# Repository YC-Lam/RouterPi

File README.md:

# RouterPi

A modular router development board based on the raspberry pi compute module 5.

Features:
- 2x 2.5G Ethernet Wan/Lan port
- 2x Gigabyte Ethernet Lan port
- M.2 E key connector for AP module
- RTC battery
- PWM fan connector
- SD card slot for compute module lite
- 12-24v input voltage

# Design constraints
- minimal track width: 0.127 mm
- minimal clearance: 0.125 mm
- minimal via hole diameter: 0.3 mm
- minimal via ring diameter: 0.45 mm

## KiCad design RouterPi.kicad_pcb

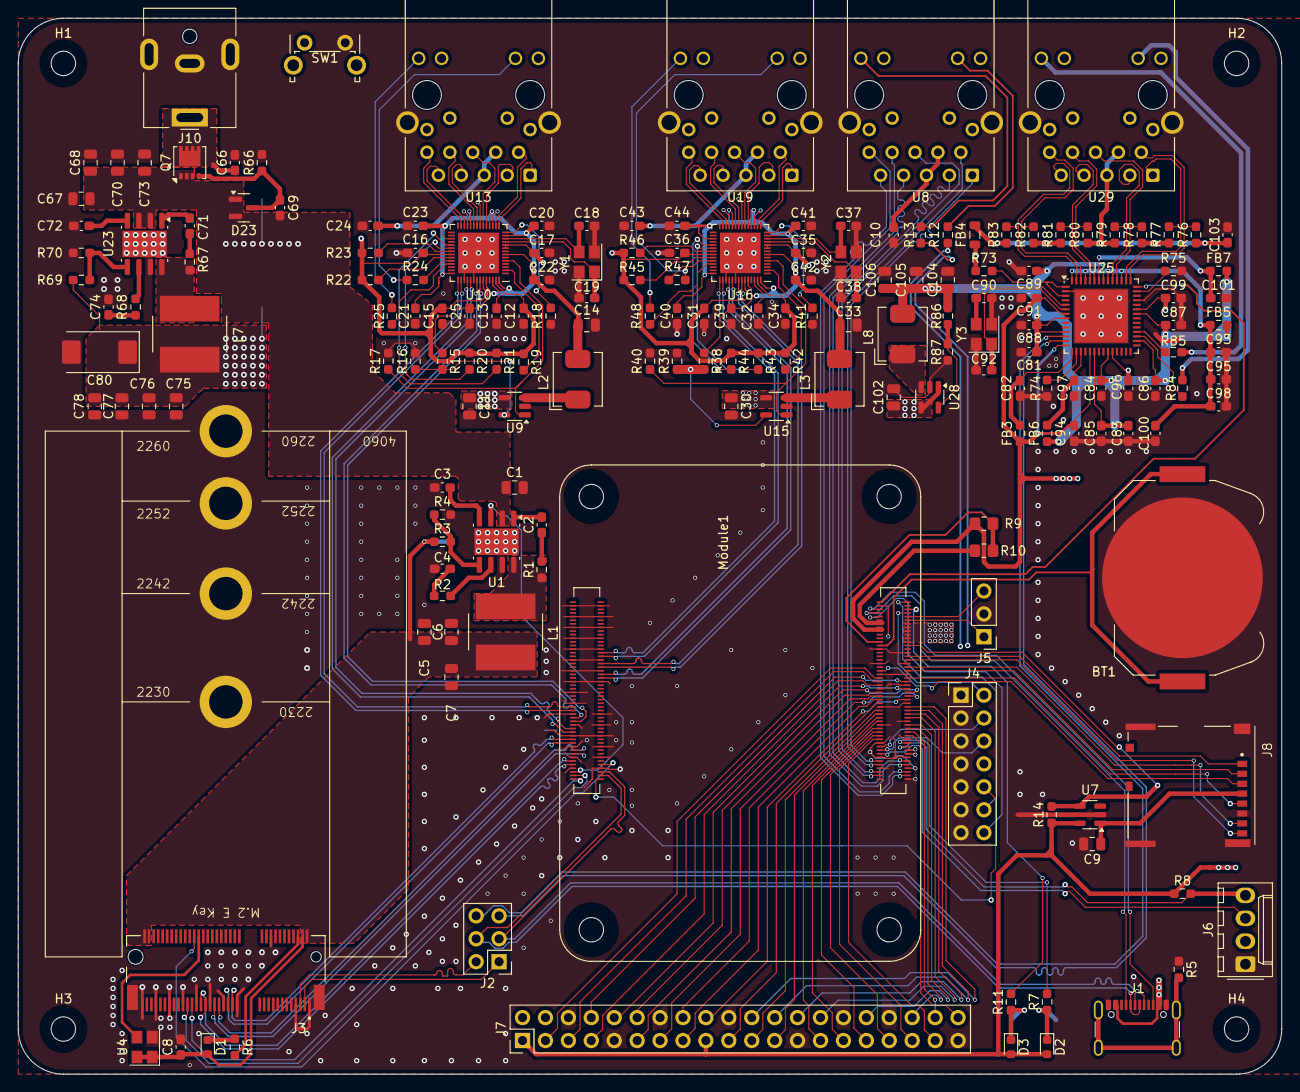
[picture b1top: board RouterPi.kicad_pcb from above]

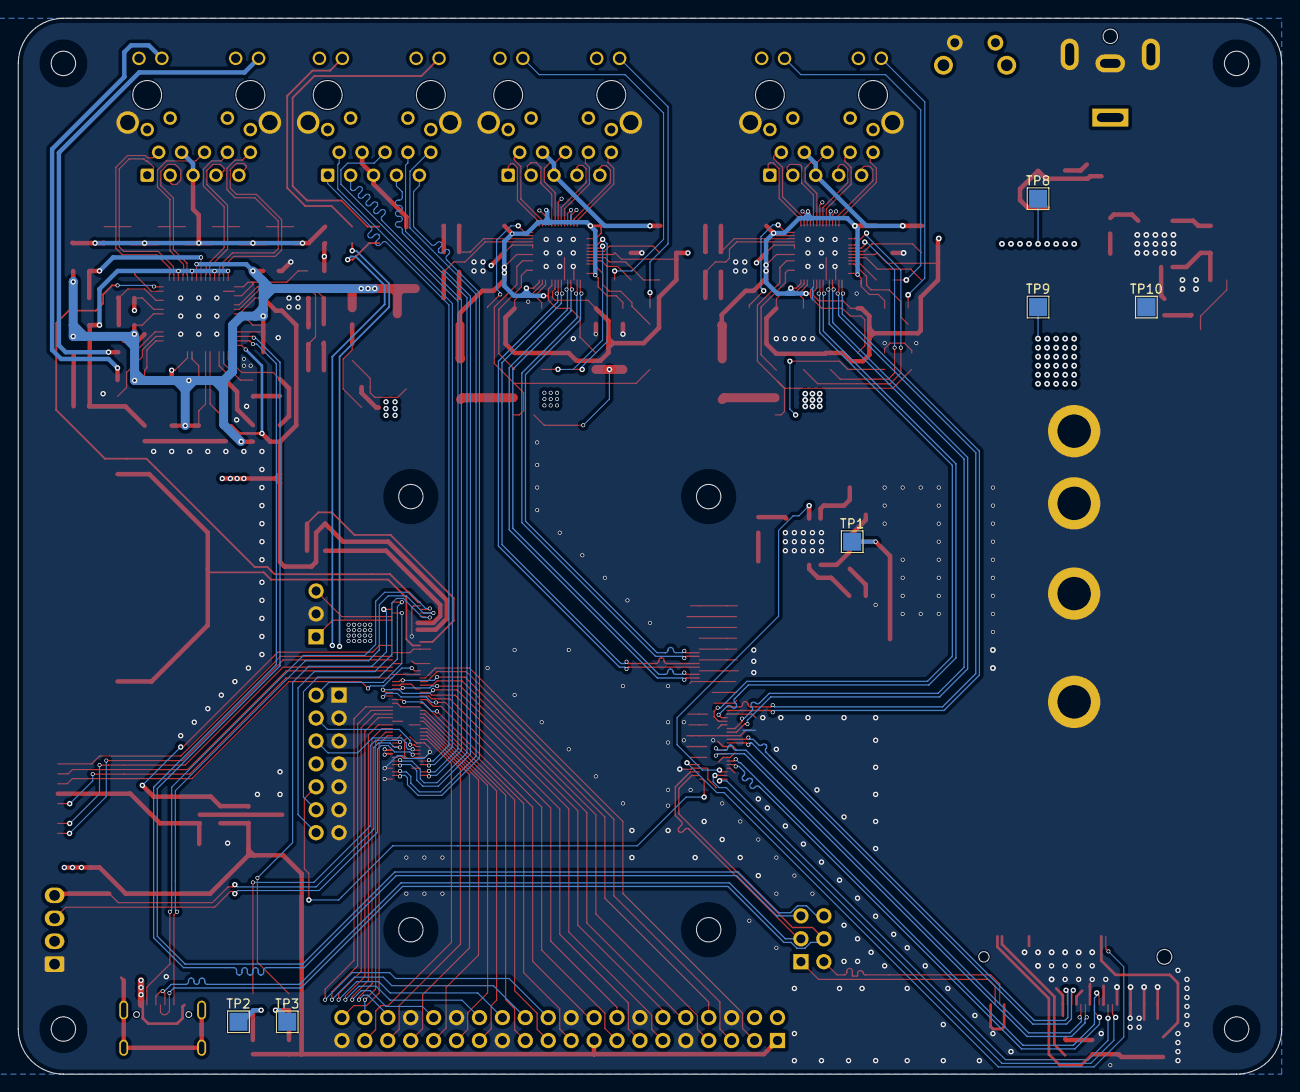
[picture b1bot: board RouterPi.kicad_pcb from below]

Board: 4 copper layers, 140.0 x 117.0 mm, 192 parts (6 on the bottom side), 199 nets.

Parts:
BT1: Battery_Cell; BatteryHolder_Keystone_3034_1x20mm
C1, C67, C68, C70, C73: 10uF 35v; C_0805_2012Metric
C2, C3, C8, C10, C12, C13, C15, C16, C17, C20, C21, C22, C23, C24, C25, C31, C32, C34, C35, C36, C39, C40, C41, C42, C43, C44, C71, C72, C81, C82, C83, C84, C85, C86, C87, C88, C89, C91, C93, C94, C95, C96, C97, C98, C99, C100, C101, C103: 100nF; C_0603_1608Metric_Pad1.08x0.95mm_HandSolder
C4: 2.7nF; C_0603_1608Metric_Pad1.08x0.95mm_HandSolder
C5, C6, C7: 22uF; C_0805_2012Metric
C9, C75, C76, C77, C78, C104, C105, C106: 10uF; C_0805_2012Metric
C11, C30, C102: 4.7uF; C_0805_2012Metric
C14, C33: 47uF; C_0805_2012Metric
C18, C19, C37, C38, C90, C92: 15pF; C_0603_1608Metric_Pad1.08x0.95mm_HandSolder
C66: 100nF 100v; C_0603_1608Metric_Pad1.08x0.95mm_HandSolder
C69: 100nF 35v; C_0603_1608Metric_Pad1.08x0.95mm_HandSolder
C74: 1.2nF; C_0603_1608Metric_Pad1.08x0.95mm_HandSolder
C80: 100uF; CP_EIA-7343-31_Kemet-D
D1, D2: LED Green; LED_0603_1608Metric
D3: LED Red; LED_0603_1608Metric
D23: MMBZ5242BLT3G; SOT-23
FB3, FB5, FB6, FB7: 120 ohms@100MHz; R_0603_1608Metric_Pad0.98x0.95mm_HandSolder
FB4: 220 ohms@100MHz; L_0805_2012Metric
H1, H2, H3, H4: MountingHole; MountingHole_2.7mm_M2.5_DIN965
J1: GCT_USB4105-GF-A; USB_C_Receptacle_GCT_USB4105-xx-A_16P_TopMnt_Horizontal
J2: USB SEL; PinHeader_2x03_P2.54mm_Vertical
J3: Bus_M.2_Socket_E; AMPHENOL_MDT420E03001
J4: Conn_02x07_Odd_Even; PinHeader_2x07_P2.54mm_Vertical
J5: Conn_01x03; PinHeader_1x03_P2.54mm_Vertical
J6: Molex_KK-254_AE-6410-04A; Molex_KK-254_AE-6410-04A_1x04_P2.54mm_Vertical
J7: THD-20-R; PinHeader_2x20_P2.54mm_Vertical
J8: Micro_SD_Card_Det; SDCARD_MOLEX_503398-1892
J10: Barrel_Jack; BarrelJack_CUI_PJ-063AH_Horizontal
L1, L7: 3.3uH; L_Bourns_SRN8040TA
L2, L3, L8: 2.2uH; L_Bourns_SRP5030CC
Module1: ComputeModule5-CM5; Raspberry-Pi-5-Compute-Module
Q7: DMP3013SFV-7; Diodes_PowerDI3333-8
R1, R67: 10R; R_0603_1608Metric_Pad0.98x0.95mm_HandSolder
R2: 10.5k 1%; R_0603_1608Metric_Pad0.98x0.95mm_HandSolder
R3: 69.8K 1%; R_0603_1608Metric_Pad0.98x0.95mm_HandSolder
R4: 22.1K 1%; R_0603_1608Metric_Pad0.98x0.95mm_HandSolder
R5: 10M; R_0603_1608Metric_Pad0.98x0.95mm_HandSolder
R6, R7, R11: 1k; R_0603_1608Metric_Pad0.98x0.95mm_HandSolder
R8, R14: 10K 1%; R_0603_1608Metric_Pad0.98x0.95mm_HandSolder
R9: 0R; R_0805_2012Metric_Pad1.20x1.40mm_HandSolder
R10: nf; R_0805_2012Metric_Pad1.20x1.40mm_HandSolder
R12, R13, R24, R25, R47, R48, R84, R85: 470R; R_0603_1608Metric_Pad0.98x0.95mm_HandSolder
R15, R38: 57.6k; R_0603_1608Metric_Pad0.98x0.95mm_HandSolder
R16, R39, R86, R87: 100k; R_0603_1608Metric_Pad0.98x0.95mm_HandSolder
R17, R19, R20, R21, R22, R23, R40, R42, R43, R44, R45, R46, R73: 10k; R_0603_1608Metric_Pad0.98x0.95mm_HandSolder
R18, R41: 2.49k; R_0603_1608Metric_Pad0.98x0.95mm_HandSolder
R66, R69: 12K 1%; R_0603_1608Metric_Pad0.98x0.95mm_HandSolder
R68: 20K 1%; R_0603_1608Metric_Pad0.98x0.95mm_HandSolder
R70: 2.2K 1%; R_0603_1608Metric_Pad0.98x0.95mm_HandSolder
R74: 12k 1%; R_0603_1608Metric_Pad0.98x0.95mm_HandSolder
R75: 8.06k 1%; R_0603_1608Metric_Pad0.98x0.95mm_HandSolder
R76, R77, R78, R79, R80, R81, R82, R83: 49.9R; R_0603_1608Metric_Pad0.98x0.95mm_HandSolder
SW1: Right angle Tact button; SW_Tactile_SPST_Angled_PTS645Vx58-2LFS
TP1, TP2, TP3, TP8, TP9, TP10: TestPoint; TestPoint_Pad_2.0x2.0mm
U1, U23: AP64501SP-13; SOIC-8-1EP_3.9x4.9mm_P1.27mm_EP2.95x4.9mm_Mask2.71x3.4mm
U2, U3: Amphenol_10164227-1001A1RLF; Amphenol_10164227-1001A1RLF_placeholder
U4: ASEK-32.768KHZ-L-R-T; Crystal_SMD_3225-4Pin_3.2x2.5mm
U7: RT9742GGJ5; SOT-23-5
U8, U13, U19, U29: MagJack-A70-112-331N126; TRJG0926HENL
U9, U15, U28: TLV62569DBVR; SOT-23-5
U10, U16: RTL8156BG; QFN-56_EP_6x6_Pitch0.35mm
U25: LAN7500-ABJZ; QFN-56-1EP_8x8mm_P0.5mm_EP5.9x5.9mm
Y1, Y2, Y3: 25MHz; Crystal_SMD_3225-4Pin_3.2x2.5mm

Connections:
/2.5G_ETHERNET_LAN/DVDD09: C33.1, C39.1, C40.1, C41.1, C42.1, C44.1, L3.2, R38.1, U16.7 (DVDD09), U16.13 (AVDD09), U16.18 (AVDD09), U16.24 (AVDD09), U16.31 (DVDD09), U16.42 (VDD09_USB), U16.52 (VDD09_USB), U16.56 (DVDD09)
/2.5G_ETHERNET_LAN/DVDD09_EN: R40.1, U15.1 (EN), U16.5 (POW_EXT_SWR)
/2.5G_ETHERNET_LAN/ETH_LEDG: R47.2, U16.38 (LED0/EEDI/SPISI)
/2.5G_ETHERNET_LAN/ETH_LEDY: R48.2, U16.39 (LED1/EESK/SPISCK)
/2.5G_ETHERNET_LAN/TRD0_N: U16.16 (MDIN0), U19.2 (TRD0-)
/2.5G_ETHERNET_LAN/TRD0_P: U16.15 (MDIP0), U19.1 (TRD0+)
/2.5G_ETHERNET_LAN/TRD1_N: U16.20 (MDIN1), U19.6 (TRD1-)
/2.5G_ETHERNET_LAN/TRD1_P: U16.19 (MDIP1), U19.3 (TRD1+)
/2.5G_ETHERNET_LAN/TRD2_N: U16.23 (MDIN2), U19.8 (TRD2-)
/2.5G_ETHERNET_LAN/TRD2_P: U16.22 (MDIP2), U19.7 (TRD2+)
/2.5G_ETHERNET_LAN/TRD3_N: U16.27 (MDIN3), U19.10 (TRD3-)
/2.5G_ETHERNET_LAN/TRD3_P: U16.26 (MDIP3), U19.9 (TRD3+)
/2.5G_ETHERNET_LAN/USB3_D_N: Module1.165 (USB3-1-D_N), U16.49 (DM)
/2.5G_ETHERNET_LAN/USB3_D_P: Module1.163 (USB3-1-D_P), U16.50 (DP)
/2.5G_ETHERNET_LAN/USB3_RXN: Module1.157 (USB3-1-RX_N), U16.47 (SSRXN)
/2.5G_ETHERNET_LAN/USB3_RXP: Module1.159 (USB3-1-RX_P), U16.46 (SSRXP)
/2.5G_ETHERNET_LAN/USB3_TXN: Module1.169 (USB3-1-TX_N), U16.44 (SSTXN)
/2.5G_ETHERNET_LAN/USB3_TXP: Module1.171 (USB3-1-TX_P), U16.43 (SSTXP)
/2.5G_ETHERNET_LAN/XIN: C37.1, U16.12 (CKXTAL1), Y2.3
/2.5G_ETHERNET_LAN/XOUT: C38.1, U16.11 (CKXTAL2), Y2.1
/2.5G_ETHERNET_WAN/DVDD09: C14.1, C20.1, C21.1, C22.1, C23.1, C25.1, L2.2, R15.1, U10.7 (DVDD09), U10.13 (AVDD09), U10.18 (AVDD09), U10.24 (AVDD09), U10.31 (DVDD09), U10.42 (VDD09_USB), U10.52 (VDD09_USB), U10.56 (DVDD09)
/2.5G_ETHERNET_WAN/DVDD09_EN: R17.1, U9.1 (EN), U10.5 (POW_EXT_SWR)
/2.5G_ETHERNET_WAN/ETH_LEDG: R24.2, U10.38 (LED0/EEDI/SPISI)
/2.5G_ETHERNET_WAN/ETH_LEDY: R25.2, U10.39 (LED1/EESK/SPISCK)
/2.5G_ETHERNET_WAN/TRD0_N: U10.16 (MDIN0), U13.2 (TRD0-)
/2.5G_ETHERNET_WAN/TRD0_P: U10.15 (MDIP0), U13.1 (TRD0+)
/2.5G_ETHERNET_WAN/TRD1_N: U10.20 (MDIN1), U13.6 (TRD1-)
/2.5G_ETHERNET_WAN/TRD1_P: U10.19 (MDIP1), U13.3 (TRD1+)
/2.5G_ETHERNET_WAN/TRD2_N: U10.23 (MDIN2), U13.8 (TRD2-)
/2.5G_ETHERNET_WAN/TRD2_P: U10.22 (MDIP2), U13.7 (TRD2+)
/2.5G_ETHERNET_WAN/TRD3_N: U10.27 (MDIN3), U13.10 (TRD3-)
/2.5G_ETHERNET_WAN/TRD3_P: U10.26 (MDIP3), U13.9 (TRD3+)
/2.5G_ETHERNET_WAN/USB3_D_N: Module1.136 (USB3-0-D_N), U10.49 (DM)
/2.5G_ETHERNET_WAN/USB3_D_P: Module1.134 (USB3-0-D_P), U10.50 (DP)
/2.5G_ETHERNET_WAN/USB3_RXN: Module1.130 (USB3-0-RX_P), U10.47 (SSRXN)
/2.5G_ETHERNET_WAN/USB3_RXP: Module1.128 (USB3-0-RX_N), U10.46 (SSRXP)
/2.5G_ETHERNET_WAN/USB3_TXN: Module1.142 (USB3-0-TX_P), U10.44 (SSTXN)
/2.5G_ETHERNET_WAN/USB3_TXP: Module1.140 (USB3-0-TX_N), U10.43 (SSTXP)
/2.5G_ETHERNET_WAN/XIN: C18.1, U10.12 (CKXTAL1), Y1.3
/2.5G_ETHERNET_WAN/XOUT: C19.1, U10.11 (CKXTAL2), Y1.1
/1000M_ETHERNET_LAN/+1.2v: C81.1, C83.1, C84.1, C85.1, C86.1, C87.1, C88.1, C89.1, C104.1, C105.1, C106.1, FB5.2, FB6.1, FB7.2, L8.2, R86.1, U25.8 (VDD12CORE), U25.11 (VDD12CORE), U25.20 (VDD12CORE), U25.23 (VDD12CORE), U25.30 (VDD12CORE), U25.36 (VDD12CORE), U25.49 (VDD12BIAS)
/1000M_ETHERNET_LAN/CT: C103.1, FB4.2, R76.1, R77.1, R78.1, R79.1, R80.1, R81.1, R82.1, R83.1, U29.4 (CT), U29.5 (CT)
/1000M_ETHERNET_LAN/ETH_LEDG: R84.2, U25.31 (GPIO0)
/1000M_ETHERNET_LAN/ETH_LEDY: R85.2, U25.32 (GPIO1)
/1000M_ETHERNET_LAN/TRD0_N: R76.2, U25.43 (TR0N), U29.2 (TRD0-)
/1000M_ETHERNET_LAN/TRD0_P: R77.2, U25.44 (TR0P), U29.1 (TRD0+)
/1000M_ETHERNET_LAN/TRD1_N: R78.2, U25.46 (TR1N), U29.6 (TRD1-)
/1000M_ETHERNET_LAN/TRD1_P: R79.2, U25.47 (TR1P), U29.3 (TRD1+)
/1000M_ETHERNET_LAN/TRD2_N: R80.2, U25.51 (TR2N), U29.8 (TRD2-)
/1000M_ETHERNET_LAN/TRD2_P: R81.2, U25.52 (TR2P), U29.7 (TRD2+)
/1000M_ETHERNET_LAN/TRD3_N: R82.2, U25.54 (TR3N), U29.10 (TRD3-)
/1000M_ETHERNET_LAN/TRD3_P: R83.2, U25.55 (TR3P), U29.9 (TRD3+)
/1000M_ETHERNET_LAN/USB2_D_N: J2.6, U25.12 (USBDM)
/1000M_ETHERNET_LAN/USB2_D_P: J2.5, U25.13 (USBDP)
/1000M_ETHERNET_LAN/VDD12A: C93.1, C95.1, C98.1, C100.1, FB5.1, U25.45 (VDD12A), U25.48 (VDD12A), U25.53 (VDD12A), U25.56 (VDD12A)
/1000M_ETHERNET_LAN/VDD12PLL: C101.1, FB7.1, U25.50 (VDD12PLL)
/1000M_ETHERNET_LAN/VDD12USBPLL: C97.1, FB6.2, U25.17 (VDD12USBPLL)
/1000M_ETHERNET_LAN/XIN: C90.1, U25.5 (XI), Y3.3
/1000M_ETHERNET_LAN/XOUT: C92.1, U25.6 (XO), Y3.1
/+3.3v: C12.1, C15.1, C16.1, C17.1, C31.1, C34.1, C35.1, C36.1, C91.1, C94.1, C96.1, C99.1, D2.2 (A), D3.2 (A), FB3.1, FB4.1, J7.1, J7.17, Module1.84 (+3.3v_(Output)), Module1.86 (+3.3v_(Output)), R8.1, R9.1, R14.1, R19.1, R20.1, R21.1, R22.1, R23.1, R42.1, R43.1, R44.1, R45.1, R46.1, R73.1, U7.5 (IN), U8.15 (LEDY_A), U8.17 (LEDG_A), U10.9 (AVDD33), U10.10 (AVDD33_XTAL), U10.17 (AVDD33), U10.21 (AVDD33), U10.25 (AVDD33), U10.36 (DVDD33), U10.51 (VDD33_USB), U10.55 (DVDD33_UPS), U13.15 (LEDY_A), U13.17 (LEDG_A), U16.9 (AVDD33), U16.10 (AVDD33_XTAL), U16.17 (AVDD33), U16.21 (AVDD33), U16.25 (AVDD33), U16.36 (DVDD33), U16.51 (VDD33_USB), U16.55 (DVDD33_UPS), U19.15 (LEDY_A), U19.17 (LEDG_A), U25.7 (VDDVARIO), U25.14 (VBUS_DET), U25.19 (VDDVARIO), U25.24 (VDDVARIO), U25.37 (VDDVARIO), U29.15 (LEDY_A), U29.17 (LEDG_A)
/+5v: C11.1, C30.1, C75.1, C76.1, C77.1, C78.1, C80.1, C102.1, J1.A4 (VBUS), J1.A9 (VBUS), J1.B4 (VBUS), J1.B9 (VBUS), J7.2, J7.4, L7.2, Module1.77 (+5v_(Input)), Module1.79 (+5v_(Input)), Module1.81 (+5v_(Input)), Module1.83 (+5v_(Input)), Module1.85 (+5v_(Input)), Module1.87 (+5v_(Input)), R69.1, TP9.1, U9.4 (VIN), U15.4 (VIN), U28.1 (EN), U28.4 (VIN)
/+12v: C1.1, C67.1, C68.1, C69.1, C70.1, C73.1, D23.1 (K), D23.2 (K), J6.2, Q7.1 (S), Q7.2 (S), Q7.3 (S), TP8.1, U1.2 (VIN), U23.2 (VIN), U23.3 (EN)
/CM5_GPIO ( Ethernet, GPIO, SDCARD)/+1.8v: Module1.88 (+1.8v_(Output)), Module1.90 (+1.8v_(Output)), R10.1
/CM5_GPIO ( Ethernet, GPIO, SDCARD)/BT_nDis: J5.3, Module1.91 (BT_nDisable)
/CM5_GPIO ( Ethernet, GPIO, SDCARD)/CC1: J1.A5 (CC1), Module1.94 (CC1)
/CM5_GPIO ( Ethernet, GPIO, SDCARD)/CC2: J1.B5 (CC2), Module1.96 (CC2)
/CM5_GPIO ( Ethernet, GPIO, SDCARD)/EEPROM_nWP: J4.4, Module1.20 (EEPROM_nWP)
/CM5_GPIO ( Ethernet, GPIO, SDCARD)/ETH_LEDG: Module1.17 (Ethernet_nLED2(3.3v)), R12.2
/CM5_GPIO ( Ethernet, GPIO, SDCARD)/ETH_LEDY: Module1.15 (Ethernet_nLED3(3.3v)), R13.2
/CM5_GPIO ( Ethernet, GPIO, SDCARD)/GPIO2: J7.3, Module1.58 (GPIO2)
/CM5_GPIO ( Ethernet, GPIO, SDCARD)/GPIO3: J7.5, Module1.56 (GPIO3)
/CM5_GPIO ( Ethernet, GPIO, SDCARD)/GPIO4: J7.7, Module1.54 (GPIO4)
/CM5_GPIO ( Ethernet, GPIO, SDCARD)/GPIO5: J7.29, Module1.34 (GPIO5)
/CM5_GPIO ( Ethernet, GPIO, SDCARD)/GPIO6: J7.31, Module1.30 (GPIO6)
/CM5_GPIO ( Ethernet, GPIO, SDCARD)/GPIO7: J7.26, Module1.37 (GPIO7)
/CM5_GPIO ( Ethernet, GPIO, SDCARD)/GPIO8: J7.24, Module1.39 (GPIO8)
/CM5_GPIO ( Ethernet, GPIO, SDCARD)/GPIO9: J7.21, Module1.40 (GPIO9)
/CM5_GPIO ( Ethernet, GPIO, SDCARD)/GPIO10: J7.19, Module1.44 (GPIO10)
/CM5_GPIO ( Ethernet, GPIO, SDCARD)/GPIO11: J7.23, Module1.38 (GPIO11)
/CM5_GPIO ( Ethernet, GPIO, SDCARD)/GPIO12: J7.32, Module1.31 (GPIO12)
/CM5_GPIO ( Ethernet, GPIO, SDCARD)/GPIO13: J7.33, Module1.28 (GPIO13)
/CM5_GPIO ( Ethernet, GPIO, SDCARD)/GPIO14: J7.8, Module1.55 (GPIO14)
/CM5_GPIO ( Ethernet, GPIO, SDCARD)/GPIO15: J7.10, Module1.51 (GPIO15)
/CM5_GPIO ( Ethernet, GPIO, SDCARD)/GPIO16: J7.36, Module1.29 (GPIO16)
/CM5_GPIO ( Ethernet, GPIO, SDCARD)/GPIO17: J7.11, Module1.50 (GPIO17)
/CM5_GPIO ( Ethernet, GPIO, SDCARD)/GPIO18: J7.12, Module1.49 (GPIO18)
/CM5_GPIO ( Ethernet, GPIO, SDCARD)/GPIO19: J7.35, Module1.26 (GPIO19)
/CM5_GPIO ( Ethernet, GPIO, SDCARD)/GPIO20: J7.38, Module1.27 (GPIO20)
/CM5_GPIO ( Ethernet, GPIO, SDCARD)/GPIO21: J7.40, Module1.25 (GPIO21)
/CM5_GPIO ( Ethernet, GPIO, SDCARD)/GPIO22: J7.15, Module1.46 (GPIO22)
/CM5_GPIO ( Ethernet, GPIO, SDCARD)/GPIO23: J7.16, Module1.47 (GPIO23)
/CM5_GPIO ( Ethernet, GPIO, SDCARD)/GPIO24: J7.18, Module1.45 (GPIO24)
/CM5_GPIO ( Ethernet, GPIO, SDCARD)/GPIO25: J7.22, Module1.41 (GPIO25)
/CM5_GPIO ( Ethernet, GPIO, SDCARD)/GPIO26: J7.37, Module1.24 (GPIO26)
/CM5_GPIO ( Ethernet, GPIO, SDCARD)/GPIO27: J7.13, Module1.48 (GPIO27)
/CM5_GPIO ( Ethernet, GPIO, SDCARD)/GPIO_VREF: Module1.78 (GPIO_VREF(1.8v/3.3v_Input)), R9.2, R10.2
/CM5_GPIO ( Ethernet, GPIO, SDCARD)/ID_SC: J7.28, Module1.35 (ID_SC)
/CM5_GPIO ( Ethernet, GPIO, SDCARD)/ID_SD: J7.27, Module1.36 (ID_SD)
/CM5_GPIO ( Ethernet, GPIO, SDCARD)/PMIC_ENABLE: J4.12, Module1.99 (PMIC_ENABLE)
/CM5_GPIO ( Ethernet, GPIO, SDCARD)/PWM: J6.4, Module1.19 (FAN_PWM), R8.2
/CM5_GPIO ( Ethernet, GPIO, SDCARD)/PWR_BUT: J4.14, Module1.92 (PWR_BUT), SW1.1
/CM5_GPIO ( Ethernet, GPIO, SDCARD)/SD_CLK: J8.5 (CLK), Module1.57 (SD_CLK)
/CM5_GPIO ( Ethernet, GPIO, SDCARD)/SD_CMD: J8.3 (CMD), Module1.62 (SD_CMD)
/CM5_GPIO ( Ethernet, GPIO, SDCARD)/SD_DAT0: J8.7 (DAT0), Module1.63 (SD_DAT0)
/CM5_GPIO ( Ethernet, GPIO, SDCARD)/SD_DAT1: J8.8 (DAT1), Module1.67 (SD_DAT1)
/CM5_GPIO ( Ethernet, GPIO, SDCARD)/SD_DAT2: J8.1 (DAT2), Module1.69 (SD_DAT2)
/CM5_GPIO ( Ethernet, GPIO, SDCARD)/SD_DAT3: J8.2 (DAT3/CD), Module1.61 (SD_DAT3)
/CM5_GPIO ( Ethernet, GPIO, SDCARD)/SD_PWR: C9.1, J8.4 (VDD), U7.1 (OUT)
/CM5_GPIO ( Ethernet, GPIO, SDCARD)/SD_PWR_ON: Module1.75 (SD_PWR_ON), R14.2, U7.4 (EN)
/CM5_GPIO ( Ethernet, GPIO, SDCARD)/SYNC_OUT: J4.6, Module1.18 (Ethernet_SYNC_OUT(3.3v))
/CM5_GPIO ( Ethernet, GPIO, SDCARD)/TACHO: J6.3, Module1.16 (FAN_TACHO)
/CM5_GPIO ( Ethernet, GPIO, SDCARD)/TRD0_N: Module1.10 (Ethernet_Pair0_N), U8.2 (TRD0-)
/CM5_GPIO ( Ethernet, GPIO, SDCARD)/TRD0_P: Module1.12 (Ethernet_Pair0_P), U8.1 (TRD0+)
/CM5_GPIO ( Ethernet, GPIO, SDCARD)/TRD1_N: Module1.6 (Ethernet_Pair1_N), U8.6 (TRD1-)
/CM5_GPIO ( Ethernet, GPIO, SDCARD)/TRD1_P: Module1.4 (Ethernet_Pair1_P), U8.3 (TRD1+)
/CM5_GPIO ( Ethernet, GPIO, SDCARD)/TRD2_N: Module1.9 (Ethernet_Pair2_N), U8.8 (TRD2-)
/CM5_GPIO ( Ethernet, GPIO, SDCARD)/TRD2_P: Module1.11 (Ethernet_Pair2_P), U8.7 (TRD2+)
/CM5_GPIO ( Ethernet, GPIO, SDCARD)/TRD3_N: Module1.5 (Ethernet_Pair3_N), U8.10 (TRD3-)
/CM5_GPIO ( Ethernet, GPIO, SDCARD)/TRD3_P: Module1.3 (Ethernet_Pair3_P), U8.9 (TRD3+)
/CM5_GPIO ( Ethernet, GPIO, SDCARD)/USBOTG: J4.10, Module1.101 (USB_OTG_ID)
/CM5_GPIO ( Ethernet, GPIO, SDCARD)/VBAT: BT1.1 (+), Module1.76 (VBAT)
/CM5_GPIO ( Ethernet, GPIO, SDCARD)/WL_nDis: J5.1, Module1.89 (WiFi_nDisable)
/CM5_GPIO ( Ethernet, GPIO, SDCARD)/nPWR_LED: Module1.95 (LED_nPWR), R11.2
/CM5_GPIO ( Ethernet, GPIO, SDCARD)/nRPIBOOT: J4.2, Module1.93 (nRPIBOOT)
/CM5_HighSpeed/M2_3v3: C5.1, C6.1, C7.1, C8.1, D1.2 (A), J3.2 (3.3V), J3.4 (3.3V), J3.72 (3.3V), J3.74 (3.3V), L1.2, R3.1, TP1.1, U4.1 (EN), U4.4 (VDD)
/CM5_HighSpeed/PCIE_CLK_N: J3.49 (REFCLKn0), Module1.112 (PCIe_CLK_N)
/CM5_HighSpeed/PCIE_CLK_P: J3.47 (REFCLKp0), Module1.110 (PCIe_CLK_P)
/CM5_HighSpeed/PCIE_PWR_EN: Module1.106 (PCIE_PWR_EN), U1.3 (EN)
/CM5_HighSpeed/PCIE_RX_N: J3.41 (PERp0), Module1.118 (PCIe_RX_N)
/CM5_HighSpeed/PCIE_RX_P: J3.43 (PERn0), Module1.116 (PCIe_RX_P)
/CM5_HighSpeed/PCIE_TX_N: J3.35 (PETp0), Module1.124 (PCIe_TX_N)
/CM5_HighSpeed/PCIE_TX_P: J3.37 (PETn0), Module1.122 (PCIe_TX_P)
/CM5_HighSpeed/PCIE_nCLKREQ: J3.53 (~CLKREQ0), Module1.102 (PCIe_nCLKREQ)
/CM5_HighSpeed/PCIE_nRST: J3.52 (~PERST0), Module1.109 (PCIe_nRST)
/CM5_HighSpeed/PCIE_nWAKE: J3.55 (~PEWAKE0), Module1.104 (PCIE_nWAKE)
/CM5_HighSpeed/USB2_M2_D_N: J2.2, J3.5 (USB_D-)
/CM5_HighSpeed/USB2_M2_D_P: J2.1, J3.3 (USB_D+)
/CM5_HighSpeed/USB2_N: J1.A7 (D-), J1.B7 (D-), J2.4, Module1.103 (USB2_N)
/CM5_HighSpeed/USB2_P: J1.A6 (D+), J1.B6 (D+), J2.3, Module1.105 (USB2_P)
/nEXTRST: Module1.100 (CAM_GPIO1), U25.42 (~RESET)
GND: BT1.2 (-), C1.2, C3.2, C4.2, C5.2, C6.2, C7.2, C8.2, C9.2, C10.2, C11.2, C12.2, C13.2, C14.2, C15.2, C16.2, C17.2, C18.2, C19.2, C20.2, C21.2, C22.2, C23.2, C24.2, C25.2, C30.2, C31.2, C32.2, C33.2, C34.2, C35.2, C36.2, C37.2, C38.2, C39.2, C40.2, C41.2, C42.2, C43.2, C44.2, C66.2, C67.2, C68.2, C70.2, C72.2, C73.2, C74.2, C75.2, C76.2, C77.2, C78.2, C80.2, C81.2, C82.2, C83.2, C84.2, C85.2, C86.2, C87.2, C88.2, C89.2, C90.2, C91.2, C92.2, C93.2, C94.2, C95.2, C96.2, C97.2, C98.2, C99.2, C100.2, C101.2, C102.2, C103.2, C104.2, C105.2, C106.2, J1.A1 (GND), J1.A12 (GND), J1.B1 (GND), J1.B12 (GND), J3.1 (GND), J3.7 (GND), J3.18 (GND), J3.33 (GND), J3.39 (GND), J3.45 (GND), J3.51 (GND), J3.57 (GND), J3.63 (GND), J3.69 (GND), J3.75 (GND), J3.M1 (GND2230), J3.M2 (GND2242), J3.M3 (GND2260), J3.M4 (GND2280), J3.S1, J3.S2, J4.1, J4.3, J4.5, J4.7, J4.9, J4.11, J4.13, J5.2, J6.1, J7.6, J7.9, J7.14, J7.20, J7.25, J7.30, J7.34, J7.39, J8.6 (VSS), J8.11 (SHIELD), J10.2, J10.MP (MountPin), Module1.1 (GND), Module1.2 (GND), Module1.7 (GND), Module1.8 (GND), Module1.13 (GND), Module1.14 (GND), Module1.22 (GND), Module1.23 (GND), Module1.32 (GND), Module1.33 (GND), Module1.42 (GND), Module1.43 (GND), Module1.52 (GND), Module1.53 (GND), Module1.59 (GND), Module1.60 (GND), Module1.65 (GND), Module1.66 (GND), Module1.71 (GND), Module1.74 (GND), Module1.98 (GND), Module1.107 (GND), Module1.108 (GND), Module1.113 (GND), Module1.114 (GND), Module1.119 (GND), Module1.120 (GND), Module1.125 (GND), Module1.126 (GND), Module1.131 (GND), Module1.132 (GND), Module1.137 (GND), Module1.138 (GND), Module1.144 (GND), Module1.150 (GND), Module1.155 (GND), Module1.156 (GND), Module1.161 (GND), Module1.162 (GND), Module1.167 (GND), Module1.168 (GND), Module1.173 (GND), Module1.174 (GND), Module1.179 (GND), Module1.180 (GND), Module1.185 (GND), Module1.186 (GND), Module1.191 (GND), Module1.192 (GND), Module1.197 (GND), Module1.198 (GND), R4.2, R5.1, R16.2, R17.2, R18.2, R39.2, R40.2, R41.2, R66.2, R70.2, R74.2, R75.2, R87.2, SW1.2, TP10.1, U1.7 (GND), U1.9 (EP), U4.2 (GND), U7.2 (GND), U8.19 (SHIELD), U8.20 (SHIELD), U9.2 (GND), U10.45 (GND), U10.48 (GND), U10.57 (GND), U13.19 (SHIELD), U13.20 (SHIELD), U15.2 (GND), U16.45 (GND), U16.48 (GND), U16.57 (GND), U19.19 (SHIELD), U19.20 (SHIELD), U23.7 (GND), U23.9 (EP), U25.2 (TCK), U25.39 (TEST), U25.57 (GND), U28.2 (GND), U29.19 (SHIELD), U29.20 (SHIELD), Y1.2, Y1.4, Y2.2, Y2.4, Y3.2, Y3.4
unnamed: C2.1, R1.2
unnamed: C4.1, R2.2
unnamed: C10.1, U8.4 (CT), U8.5 (CT)
unnamed: C24.1, U13.4 (CT), U13.5 (CT)
unnamed: C43.1, U19.4 (CT), U19.5 (CT)
unnamed: C71.1, R67.2
unnamed: C74.1, R68.2
unnamed: D1.1 (K), R6.1
unnamed: D2.1 (K), R7.1, TP2.1
unnamed: D3.1 (K), R11.1, TP3.1
unnamed: C69.2, D23.3 (A), Q7.4 (G), R66.1
unnamed: J1.S1 (SHIELD), R5.2
unnamed: J3.50 (SUSCLK), U4.3 (Out)
unnamed: J3.6 (~LED_1), R6.2
unnamed: Module1.21 (LED_nACT), R7.2
unnamed: C66.1, J10.1, Q7.5 (D)
unnamed: C2.2, U1.1 (BST)
unnamed: R2.1, U1.6 (COMP)
unnamed: R3.2, R4.1, U1.5 (FB)
unnamed: C3.1, U1.4 (SS)
unnamed: L1.1, R1.1, U1.8 (SW)
unnamed: R13.1, U8.18 (LEDG_K)
unnamed: R12.1, U8.16 (LEDY_K)
unnamed: R15.2, R16.1, U9.5 (FB)
unnamed: L2.1, U9.3 (SW)
unnamed: R23.2, U10.35 (CONFIG_SEQ)
unnamed: R22.2, U10.37 (DOCK_DET)
unnamed: C13.1, U10.54 (DVDD09_UPS)
unnamed: R19.2, U10.2 (GPIO0)
unnamed: R20.2, U10.34 (GPIO1/SDA)
unnamed: R21.2, U10.33 (GPIO2/SCL)
unnamed: R18.1, U10.14 (RSET)
unnamed: R25.1, U13.18 (LEDG_K)
unnamed: R24.1, U13.16 (LEDY_K)
unnamed: R38.2, R39.1, U15.5 (FB)
unnamed: L3.1, U15.3 (SW)
unnamed: R46.2, U16.35 (CONFIG_SEQ)
unnamed: R45.2, U16.37 (DOCK_DET)
unnamed: C32.1, U16.54 (DVDD09_UPS)
unnamed: R42.2, U16.2 (GPIO0)
unnamed: R43.2, U16.34 (GPIO1/SDA)
unnamed: R44.2, U16.33 (GPIO2/SCL)
unnamed: R41.1, U16.14 (RSET)
unnamed: R48.1, U19.18 (LEDG_K)
unnamed: R47.1, U19.16 (LEDY_K)
unnamed: C71.2, U23.1 (BST)
unnamed: R68.1, U23.6 (COMP)
unnamed: R69.2, R70.1, U23.5 (FB)
unnamed: C72.1, U23.4 (SS)
unnamed: L7.1, R67.1, U23.8 (SW)
unnamed: R73.2, U25.1 (TDI), U25.3 (TMS)
unnamed: C82.1, FB3.2, U25.15 (VDD33A)
unnamed: R75.1, U25.41 (ETHRBIAS)
unnamed: R74.1, U25.16 (USBRBIAS)
unnamed: R86.2, R87.1, U28.5 (FB)
unnamed: L8.1, U28.3 (SW)
unnamed: R85.1, U29.18 (LEDG_K)
unnamed: R84.1, U29.16 (LEDY_K)

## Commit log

2026-01-05 main
